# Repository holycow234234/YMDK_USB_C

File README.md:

# YMDK/Aliexpress Aluminum CNC TKL Case USB C Daughter Board:
I wanted my new keyboard to use USB C, so I made this.
This daughterboard is intended for use with [this case](https://ymdkey.com/collections/case/products/cnc-anodized-aluminum-case-shell-for-filco-cm-cooler-master-87-tenkeyless-mechanical-keyboard-including-detachable-usb-module)

Credit to sparkfun for the schematic, I used their usb C breakout board as an example.

You can desolder the cable from the daughterboard that comes with the case and use it with this board.<br />
This works with the screws included with the case, just push hard!

# BOM:
* GCT USB4105 Usb type C port
* 2x 0805 5.1k ohm resistors

I had success with 1.6mm FR4

# Render:

# Installed:

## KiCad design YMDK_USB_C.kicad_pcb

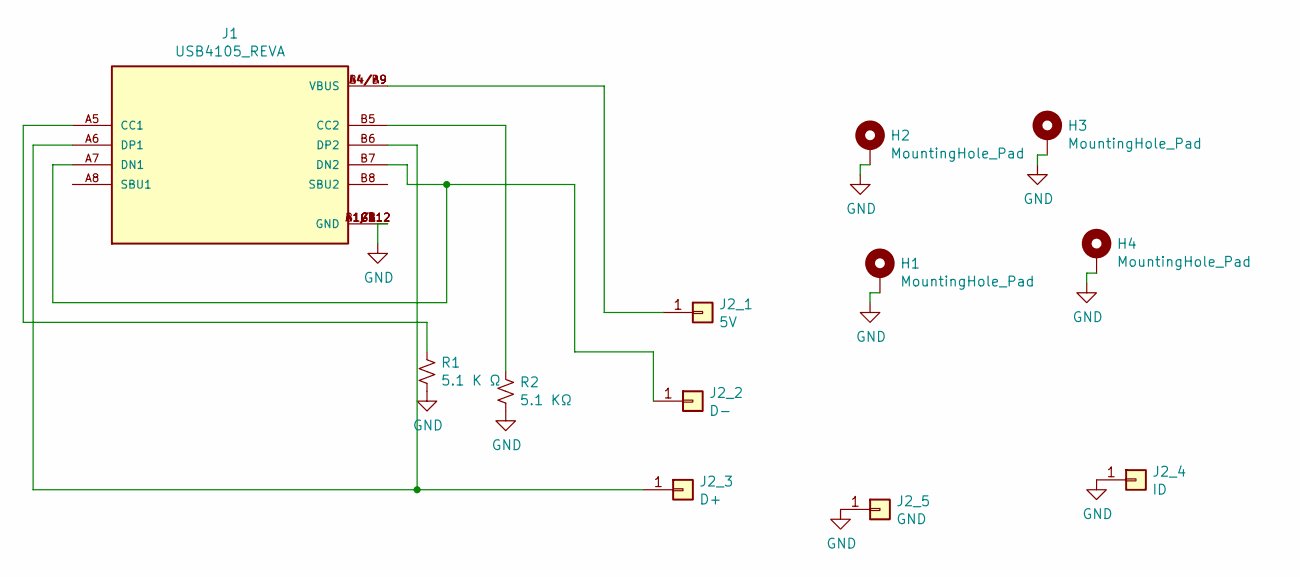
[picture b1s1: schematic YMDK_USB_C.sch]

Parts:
H1, H2, H3, H4: MountingHole_Pad; MountingHole_2.1mm_M2_Pad
J1: USB4105_REVA; GCT_USB4105_REVA; PARTREV 0.2
J2_1: 5V; SolderPad1.5x3mm
J2_2: D-; SolderPad1.5x3mm
J2_3: D+; SolderPad1.5x3mm
J2_4: ID; SolderPad1.5x3mm
J2_5: GND
R1: 5.1 K Ω; R_0805_2012Metric_Pad1.20x1.40mm_HandSolder
R2: 5.1 KΩ; R_0805_2012Metric_Pad1.20x1.40mm_HandSolder

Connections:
GND: H1.1, H2.1, H3.1, H4.1, J1.A1/B12 (GND), J1.B1/A12 (GND), J1.G1 (GND), J1.G2 (GND), J1.G3 (GND), J1.G4 (GND), J2_4.1, J2_5.1, R1.2, R2.2
unnamed: J1.A4/B9 (VBUS), J1.B4/A9 (VBUS), J2_1.1
unnamed: J1.A5 (CC1), R1.1
unnamed: J1.A6 (DP1), J1.B6 (DP2), J2_3.1
unnamed: J1.A7 (DN1), J1.B7 (DN2), J2_2.1
unnamed: J1.B5 (CC2), R2.1

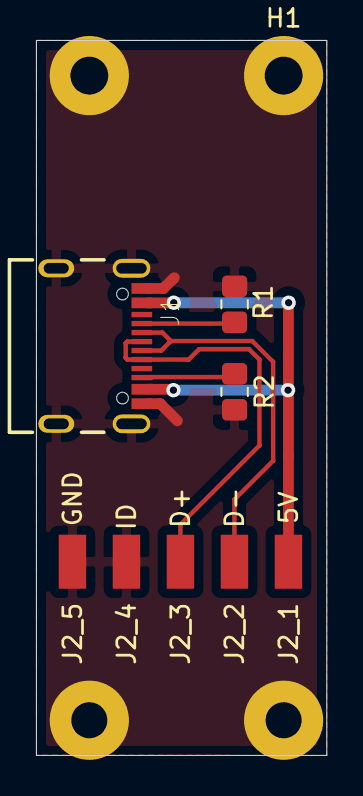
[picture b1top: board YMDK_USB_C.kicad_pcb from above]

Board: 2 copper layers, 16.1 x 39.7 mm, 12 parts (0 on the bottom side), 6 nets.
